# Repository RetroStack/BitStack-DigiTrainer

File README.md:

# DigiTrainer

As part of an introduction in digital electronics workshop at VCF SW 2024, I prepared this board. The intent was to reduce lookup time for datasheets and being able to just connect the inputs and outputs of various gates and logic ICs without caring too much about power supplies. In addition, this board features DIP-switches, a toggle and slide switch, hexadecimal switches, LED arrays which do have a built in resistor for current limiting, pull-up and -down resistors, and much more.

In addition to all of that, it includes a section for a Z80 CPU, static memory, and a ROM to be able to learn to program and work with 8-bit CPUs.

## Latest Files

In the "Latest" folder, you'll find the most up-to-date design files, including:

- Gerber files suitable for popular online PCB manufacturers like [PCBWay](/Latest/DigiTrainer_Gerber_PCBWay.zip) and [JLCPCB](/Latest/DigiTrainer_Gerber_JLCPCB.zip). Most manufacturers should be fine with either.
- A Bill of Materials (BOM) in both [CSV](/Latest/DigiTrainer_BOM.csv) and [PDF](/Latest/DigiTrainer_BOM.pdf) formats.
- The [full schematics](/Latest/DigiTrainer_Schematics.pdf) of the board.

## Implementation

The board has been implemented using KiCAD 8. The KiCAD project files are included in this repository.

## How to Use

All inputs of various ICs and gates are on the left side of the indicated gate or IC, while outputs are on the right side of the silkscreen indications. Bi-directional pins are horizontal or on the output side (such as at the Z80 CPU for the data bus).

Many components are already connected to +5V or GND and are indicated by an "arrow up" and "triangle down" respectively. Keep in mind that an LED connected to an IC output with +5V acts as an inverted output due to current sinking.

The top right area also provides a legend of common rules/laws and symbols used in digital electronics (and logic as an extension of it).

## Bill of Materials (BOM)

Below is a list of materials needed to assemble the PCB.

| Reference                                                                                                                                                                                                                                                                                                  | Qty | Description         | Footprint                                                  | Datasheet                                                    |
| ---------------------------------------------------------------------------------------------------------------------------------------------------------------------------------------------------------------------------------------------------------------------------------------------------------- | --- | ------------------- | ---------------------------------------------------------- | ------------------------------------------------------------ |
| C1,C2,C3,C4,C5,C6,C7,C8,C9,C10,C11,C12,C13,C14,C15,C16,C17,C18,C19,C20,C25,C26,C27,C28,C29,C30                                                                                                                                                                                                             | 26  | 0.1uF               | Capacitor_SMD:C_0805_2012Metric_Pad1.18x1.45mm_HandSolder  | ~                                                            |
| C21,C24                                                                                                                                                                                                                                                                                                    | 2   | 1uF                 | Capacitor_SMD:C_0805_2012Metric_Pad1.18x1.45mm_HandSolder  | ~                                                            |
| C22,C23                                                                                                                                                                                                                                                                                                    | 2   | 0.01uF              | Capacitor_SMD:C_0805_2012Metric_Pad1.18x1.45mm_HandSolder  | ~                                                            |
| D1,D2                                                                                                                                                                                                                                                                                                      | 2   | D_Schottky          | Diode_THT:D_DO-41_SOD81_P7.62mm_Horizontal                 | ~                                                            |
| DN1,DN2,DN3                                                                                                                                                                                                                                                                                                | 3   | LED Array           | Package_DIP:DIP-20_W7.62mm_Socket                          | ~                                                            |
| J1,J2,J86,J158,J159,J160                                                                                                                                                                                                                                                                                   | 6   | Conn_01x10          | Connector_PinSocket_2.54mm:PinSocket_1x10_P2.54mm_Vertical | ~                                                            |
| J3,J16,J17,J18,J19,J20,J21,J22,J23,J24,J25,J26,J27,J28,J29,J30,J31,J54,J55,J56,J57,J58,J59,J60,J61,J62,J63,J64,J65,J66,J67,J68,J69,J89,J99,J100,J102,J109,J110,J111,J112,J113,J114,J122,J123,J125,J126,J133,J137,J138,J142,J144,J145,J146,J147,J148,J149,J150,J151,J152,J153,J154,J155,J156,J157,J163,J168 | 67  | Conn_01x02          | Connector_PinSocket_2.54mm:PinSocket_1x02_P2.54mm_Vertical | ~                                                            |
| J4,J5,J6,J7,J8,J9,J10,J11,J12,J13,J14,J15,J32,J33,J34,J35,J36,J37,J38,J39,J40,J41,J42,J43,J44,J45,J46,J47,J48,J49,J50,J51,J52,J53,J70,J71,J72,J73,J74,J75,J76,J77,J78,J79,J80,J81,J87,J106,J107,J108,J135,J136,J141,J143,J167,J169                                                                         | 56  | Conn_01x03          | Connector_PinSocket_2.54mm:PinSocket_1x03_P2.54mm_Vertical | ~                                                            |
| J82,J83,J84,J85,J98,J103,J121,J124,J161,J162                                                                                                                                                                                                                                                               | 10  | Conn_01x06          | Connector_PinSocket_2.54mm:PinSocket_1x06_P2.54mm_Vertical | ~                                                            |
| J88,J90,J91,J101,J104,J105,J164,J165,J166,J173,J174                                                                                                                                                                                                                                                        | 11  | Conn_01x08          | Connector_PinSocket_2.54mm:PinSocket_1x08_P2.54mm_Vertical | ~                                                            |
| J92,J93,J94,J172                                                                                                                                                                                                                                                                                           | 4   | Conn_02x02_Odd_Even | Connector_PinHeader_2.54mm:PinHeader_2x02_P2.54mm_Vertical | ~                                                            |
| J95                                                                                                                                                                                                                                                                                                        | 1   | Barrel_Jack_Switch  | Connector_BarrelJack:BarrelJack_Horizontal                 | ~                                                            |
| J96                                                                                                                                                                                                                                                                                                        | 1   | USB_B_Mini          | Connector_USB:USB_Mini-B_Tensility_54-00023_Vertical       | ~                                                            |
| J97,J115,J117,J127,J128,J129,J130,J131,J132,J139,J140,J170,J171                                                                                                                                                                                                                                            | 13  | Conn_01x04          | Connector_PinSocket_2.54mm:PinSocket_1x04_P2.54mm_Vertical | ~                                                            |
| J116,J118,J119,J120,J134                                                                                                                                                                                                                                                                                   | 5   | Conn_01x05          | Connector_PinSocket_2.54mm:PinSocket_1x05_P2.54mm_Vertical | ~                                                            |
| R1,R2,R3                                                                                                                                                                                                                                                                                                   | 3   | 10k                 | Resistor_SMD:R_0805_2012Metric_Pad1.20x1.40mm_HandSolder   | ~                                                            |
| R4,R5,R6,R7                                                                                                                                                                                                                                                                                                | 4   | 1k                  | Resistor_SMD:R_0805_2012Metric_Pad1.20x1.40mm_HandSolder   | ~                                                            |
| RN1,RN2,RN3,RN4,RN5                                                                                                                                                                                                                                                                                        | 5   | R_Network10         | Resistor_THT:R_Array_SIP11                                 | http://www.vishay.com/docs/31509/csc.pdf                     |
| RV1                                                                                                                                                                                                                                                                                                        | 1   | R_Potentiometer     | Potentiometer_THT:Potentiometer_Bourns_3386P_Vertical      | ~                                                            |
| RV2                                                                                                                                                                                                                                                                                                        | 1   | 1M                  | Potentiometer_THT:Potentiometer_Bourns_3386P_Vertical      | ~                                                            |
| SW1,SW5,SW6,SW7,SW8                                                                                                                                                                                                                                                                                        | 5   | SW_Push             | RetroStackLibrary:SW_SPST_Push                             | ~                                                            |
| SW2                                                                                                                                                                                                                                                                                                        | 1   | SW_DPDT_x2          | RetroStackLibrary:SW_DPDT_Push                             | ~                                                            |
| SW3,SW4                                                                                                                                                                                                                                                                                                    | 2   | SW_DIP_x04          | Package_DIP:DIP-8_W7.62mm                                  | ~                                                            |
| SW9                                                                                                                                                                                                                                                                                                        | 1   | SW_SPDT             | RetroStackLibrary:SW_SPDT_Toggle                           | ~                                                            |
| SW10                                                                                                                                                                                                                                                                                                       | 1   | SW_Push_DPDT        | RetroStackLibrary:SW_DPDT_Slide_RightAngle                 | ~                                                            |
| SW11,SW12                                                                                                                                                                                                                                                                                                  | 2   | Hex Switch          | RetroStackLibrary:SW_Hexadecimal_Horizontal                | https://www.ckswitches.com/media/1333/cd.pdf                 |
| U1                                                                                                                                                                                                                                                                                                         | 1   | 74LS07              | Package_SO:SOIC-14_3.9x8.7mm_P1.27mm                       | www.ti.com/lit/ds/symlink/sn74ls07.pdf                       |
| U2                                                                                                                                                                                                                                                                                                         | 1   | 74LS04              | Package_SO:SOIC-14_3.9x8.7mm_P1.27mm                       | http://www.ti.com/lit/gpn/sn74LS04                           |
| U3                                                                                                                                                                                                                                                                                                         | 1   | 74LS266             | Package_SO:SOIC-14_3.9x8.7mm_P1.27mm                       | ~                                                            |
| U4,U5                                                                                                                                                                                                                                                                                                      | 2   | 74LS00              | Package_SO:SOIC-14_3.9x8.7mm_P1.27mm                       | http://www.ti.com/lit/gpn/sn74ls00                           |
| U6                                                                                                                                                                                                                                                                                                         | 1   | 74LS08              | Package_SO:SOIC-14_3.9x8.7mm_P1.27mm                       | http://www.ti.com/lit/gpn/sn74LS08                           |
| U7                                                                                                                                                                                                                                                                                                         | 1   | 74LS86              | Package_SO:SOIC-14_3.9x8.7mm_P1.27mm                       | 74xx/74ls86.pdf                                              |
| U8                                                                                                                                                                                                                                                                                                         | 1   | 74LS32              | Package_SO:SOIC-14_3.9x8.7mm_P1.27mm                       | http://www.ti.com/lit/gpn/sn74LS32                           |
| U9                                                                                                                                                                                                                                                                                                         | 1   | 74LS02              | Package_SO:SOIC-14_3.9x8.7mm_P1.27mm                       | http://www.ti.com/lit/gpn/sn74ls02                           |
| U10                                                                                                                                                                                                                                                                                                        | 1   | 74LS244             | Package_SO:SOIC-20W_7.5x12.8mm_P1.27mm                     | http://www.ti.com/lit/ds/symlink/sn74ls244.pdf               |
| U11                                                                                                                                                                                                                                                                                                        | 1   | 74LS245             | Package_SO:SO-20_5.3x12.6mm_P1.27mm                        | http://www.ti.com/lit/gpn/sn74LS245                          |
| U12                                                                                                                                                                                                                                                                                                        | 1   | 74LS51              | Package_SO:SOIC-14_3.9x8.7mm_P1.27mm                       | http://www.ti.com/lit/ds/symlink/sn74ls51.pdf                |
| U13                                                                                                                                                                                                                                                                                                        | 1   | 74LS174             | Package_SO:SOIC-16_3.9x9.9mm_P1.27mm                       | http://www.ti.com/lit/gpn/sn74LS174                          |
| U14                                                                                                                                                                                                                                                                                                        | 1   | 74LS175             | Package_SO:SOIC-16_3.9x9.9mm_P1.27mm                       | http://www.ti.com/lit/gpn/sn74LS175                          |
| U15                                                                                                                                                                                                                                                                                                        | 1   | 74LS373             | Package_SO:SO-20_5.3x12.6mm_P1.27mm                        | http://www.ti.com/lit/gpn/sn74LS373                          |
| U16                                                                                                                                                                                                                                                                                                        | 1   | 74LS112             | Package_SO:SOIC-16_3.9x9.9mm_P1.27mm                       | http://www.ti.com/lit/gpn/sn74LS112                          |
| U17                                                                                                                                                                                                                                                                                                        | 1   | 74LS107             | Package_SO:SOIC-14_3.9x8.7mm_P1.27mm                       | http://www.ti.com/lit/gpn/sn74LS107                          |
| U18                                                                                                                                                                                                                                                                                                        | 1   | 74LS161             | Package_SO:SOIC-16_3.9x9.9mm_P1.27mm                       | http://www.ti.com/lit/gpn/sn74LS161                          |
| U19                                                                                                                                                                                                                                                                                                        | 1   | 74LS163             | Package_SO:SOIC-16_3.9x9.9mm_P1.27mm                       | http://www.ti.com/lit/gpn/sn74LS163                          |
| U20,U21                                                                                                                                                                                                                                                                                                    | 2   | 74LS194             | Package_SO:SOIC-16_3.9x9.9mm_P1.27mm                       | http://www.ti.com/lit/gpn/sn74LS194                          |
| U22                                                                                                                                                                                                                                                                                                        | 1   | 74LS283             | Package_SO:SOIC-16_3.9x9.9mm_P1.27mm                       | http://www.ti.com/lit/gpn/sn74LS283                          |
| U23                                                                                                                                                                                                                                                                                                        | 1   | 74LS85              | Package_SO:SOIC-16_3.9x9.9mm_P1.27mm                       | http://www.ti.com/lit/gpn/sn74LS85                           |
| U24                                                                                                                                                                                                                                                                                                        | 1   | NE556               | Package_SO:SOIC-14_3.9x8.7mm_P1.27mm                       | http://www.ti.com/lit/ds/symlink/ne556.pdf                   |
| U25                                                                                                                                                                                                                                                                                                        | 1   | Z80CPU              | Package_DIP:DIP-40_W15.24mm_Socket                         | www.zilog.com/manage_directlink.php?filepath=docs/z80/um0080 |
| U26                                                                                                                                                                                                                                                                                                        | 1   | ROM_27256           | Package_DIP:DIP-28_W15.24mm                                | ~                                                            |
| U27                                                                                                                                                                                                                                                                                                        | 1   | CY7C199             | Package_DIP:DIP-28_W7.62mm                                 | ~                                                            |

## RetroStack Libraries

To work with this KiCAD project, you'll need the RetroStack libraries for KiCAD. Please [follow this link](https://www.github.com/RetroStack/KiCAD-Libraries) to access and install these libraries.

## Support this Project

RetroStack is passionate about exploring and preserving the legacy of older computer systems. BitStack is a sub-project of RetroStack, focusing on education in digital electronics. My work involves creating detailed documentation and videos to share the knowledge. I am also dedicated to reviving these classic systems by reimplementing them and offering replacement parts at no cost. If you're keen on supporting this unique project, I invite you to visit my [Patreon page](https://www.patreon.com/RetroStack). Your support would be immensely valuable and greatly appreciated!

## License

This project is licensed under the MIT License - see the [LICENSE](LICENSE) file for details.

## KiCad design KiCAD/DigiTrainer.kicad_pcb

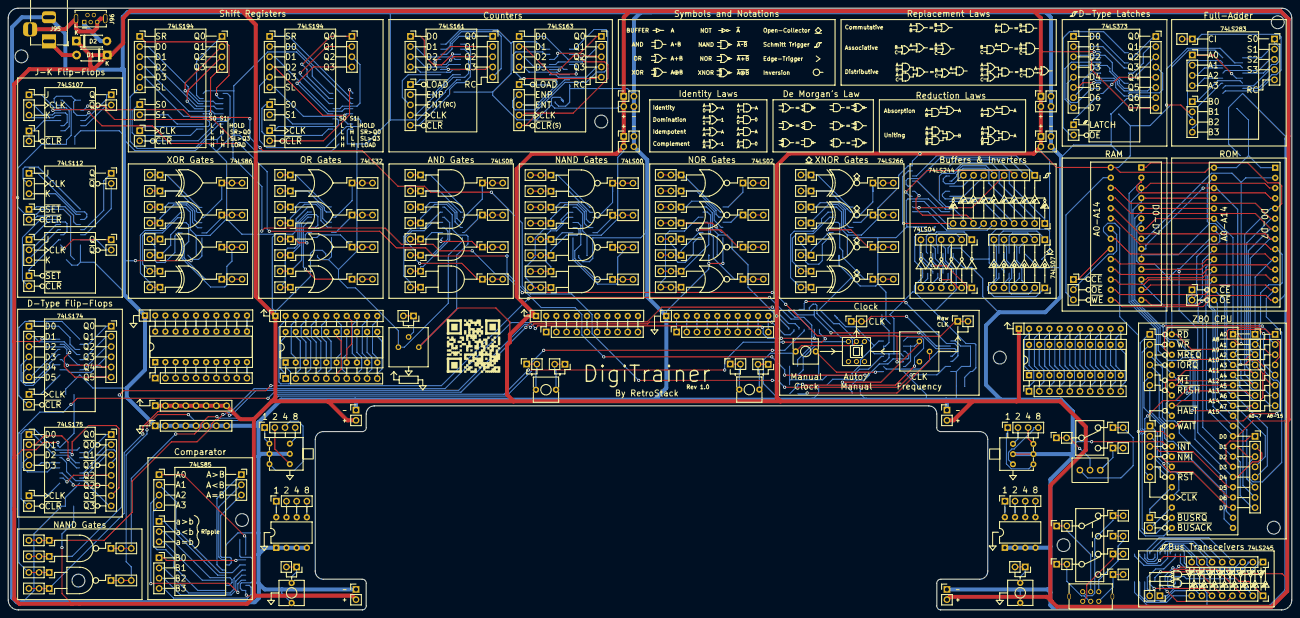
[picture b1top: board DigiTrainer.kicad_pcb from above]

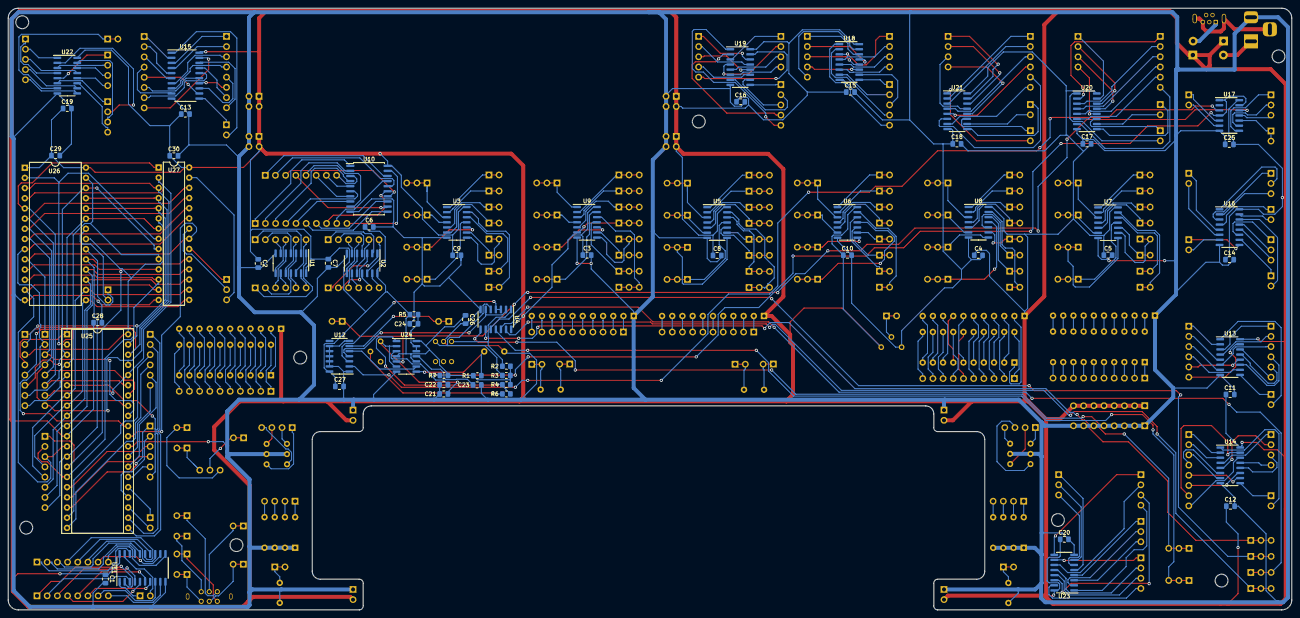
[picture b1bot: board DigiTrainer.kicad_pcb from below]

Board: 2 copper layers, 320.0 x 150.0 mm, 262 parts (64 on the bottom side), 464 nets.

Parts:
C1, C2, C3, C4, C5, C6, C7, C8, C9, C10, C11, C12, C13, C14, C15, C16, C17, C18, C19, C20, C25, C26, C27, C28, C29, C30: 0.1uF; C_0805_2012Metric_Pad1.18x1.45mm_HandSolder
C21, C24: 1uF; C_0805_2012Metric_Pad1.18x1.45mm_HandSolder
C22, C23: 0.01uF; C_0805_2012Metric_Pad1.18x1.45mm_HandSolder
D1, D2: D_Schottky; D_DO-41_SOD81_P7.62mm_Horizontal
DN1, DN2, DN3: DIP-20_W7.62mm_Socket
J1, J2, J86, J158, J159, J160: Conn_01x10; PinSocket_1x10_P2.54mm_Vertical
J3, J16, J17, J18, J19, J20, J21, J22, J23, J24, J25, J26, J27, J28, J29, J30, J31, J54, J55, J56, J57, J58, J59, J60, J61, J62, J63, J64, J65, J66, J67, J68, J69, J133, J137, J138, J142, J144, J145, J146, J147, J148, J149, J150, J151, J152, J153, J154, J155, J156, J157: PinSocket_1x02_P2.54mm_Vertical
J4, J5, J6, J7, J8, J9, J10, J11, J12, J13, J14, J15, J32, J33, J34, J35, J36, J37, J38, J39, J40, J41, J42, J43, J44, J45, J46, J47, J48, J49, J50, J51, J52, J53, J70, J71, J72, J73, J74, J75, J76, J77, J78, J79, J80, J81: PinSocket_1x03_P2.54mm_Vertical
J82, J83, J84, J85, J98, J103, J121, J124, J161, J162: Conn_01x06; PinSocket_1x06_P2.54mm_Vertical
J87, J141, J143, J169: Conn_02x01; PinHeader_1x02_P2.54mm_Vertical
J88, J90, J91, J101, J104, J105, J164, J165, J166, J173, J174: Conn_01x08; PinSocket_1x08_P2.54mm_Vertical
J89, J99, J100, J102, J109, J110, J111, J112, J113, J114, J122, J123, J125, J126, J163, J168: Conn_01x02; PinSocket_1x02_P2.54mm_Vertical
J92, J93, J94, J172: Conn_02x02_Odd_Even; PinHeader_2x02_P2.54mm_Vertical
J95: Barrel_Jack_Switch; BarrelJack_Horizontal
J96: USB_B_Mini; USB_Mini-B_Tensility_54-00023_Vertical
J97, J115, J117, J127, J128, J129, J130, J131, J132, J139, J140, J170, J171: Conn_01x04; PinSocket_1x04_P2.54mm_Vertical
J106, J107, J108, J135, J136, J167: Conn_01x03; PinSocket_1x03_P2.54mm_Vertical
J116, J118, J119, J120, J134: Conn_01x05; PinSocket_1x05_P2.54mm_Vertical
R1, R2, R3: 10k; R_0805_2012Metric_Pad1.20x1.40mm_HandSolder
R4, R5, R6, R7: 1k; R_0805_2012Metric_Pad1.20x1.40mm_HandSolder
RN1, RN2, RN3, RN4, RN5: R_Network10; R_Array_SIP11
RV1: R_Potentiometer; Potentiometer_Bourns_3386P_Vertical
RV2: 1M; Potentiometer_Bourns_3386P_Vertical
SW1, SW5, SW6, SW7, SW8: SW_Push; SW_SPST_Push
SW2: SW_DPDT_x2; SW_DPDT_Push
SW3, SW4: SW_DIP_x04; DIP-8_W7.62mm
SW9: SW_SPDT; SW_SPDT_Toggle
SW10: SW_Push_DPDT; SW_DPDT_Slide_RightAngle
SW11, SW12: SW_Hexadecimal_Horizontal
U1: 74LS07; SOIC-14_3.9x8.7mm_P1.27mm
U2: 74LS04; SOIC-14_3.9x8.7mm_P1.27mm
U3: 74LS266; SOIC-14_3.9x8.7mm_P1.27mm
U4, U5: 74LS00; SOIC-14_3.9x8.7mm_P1.27mm
U6: 74LS08; SOIC-14_3.9x8.7mm_P1.27mm
U7: 74LS86; SOIC-14_3.9x8.7mm_P1.27mm
U8: 74LS32; SOIC-14_3.9x8.7mm_P1.27mm
U9: 74LS02; SOIC-14_3.9x8.7mm_P1.27mm
U10: 74LS244; SOIC-20W_7.5x12.8mm_P1.27mm
U11: 74LS245; SO-20_5.3x12.6mm_P1.27mm
U12: 74LS51; SOIC-14_3.9x8.7mm_P1.27mm
U13: 74LS174; SOIC-16_3.9x9.9mm_P1.27mm
U14: 74LS175; SOIC-16_3.9x9.9mm_P1.27mm
U15: 74LS373; SO-20_5.3x12.6mm_P1.27mm
U16: 74LS112; SOIC-16_3.9x9.9mm_P1.27mm
U17: 74LS107; SOIC-14_3.9x8.7mm_P1.27mm
U18: 74LS161; SOIC-16_3.9x9.9mm_P1.27mm
U19: 74LS163; SOIC-16_3.9x9.9mm_P1.27mm
U20, U21: 74LS194; SOIC-16_3.9x9.9mm_P1.27mm
U22: 74LS283; SOIC-16_3.9x9.9mm_P1.27mm
U23: 74LS85; SOIC-16_3.9x9.9mm_P1.27mm
U24: NE556; SOIC-14_3.9x8.7mm_P1.27mm
U25: Z80CPU; DIP-40_W15.24mm_Socket
U26: ROM_27256; DIP-28_W15.24mm
U27: CY7C199; DIP-28_W7.62mm

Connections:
+5V: C1.1, C2.1, C3.1, C4.1, C5.1, C6.1, C7.1, C8.1, C9.1, C10.1, C11.1, C12.1, C13.1, C14.1, C15.1, C16.1, C17.1, C18.1, C19.1, C20.1, C25.1, C26.1, C27.1, C28.1, C29.1, C30.1, D1.1 (K), D2.1 (K), J87.2, J92.1, J92.3, J93.1, J93.3, J94.1, J94.3, J141.2, J143.2, J169.2, J172.1, J172.3, J173.1, J173.2, J173.3, J173.4, J173.5, J173.6, J173.7, J173.8, R1.2, R2.1, R3.2, R4.1, R5.1, R7.1, RN2.1 (common), RN3.1 (common), RN5.1 (common), RV1.1, U1.14 (VCC), U2.14 (VCC), U3.14 (VCC), U4.14 (VCC), U5.14 (VCC), U6.14 (VCC), U7.14 (VCC), U8.14 (VCC), U9.14 (VCC), U10.20 (VCC), U11.20 (VCC), U12.14 (VCC), U13.16 (VCC), U14.16 (VCC), U15.20 (VCC), U16.16 (VCC), U17.14 (VCC), U18.16 (VCC), U19.16 (VCC), U20.16 (VCC), U21.16 (VCC), U22.16 (VCC), U23.16 (VCC), U24.4 (R), U24.10 (R), U24.14 (VCC), U25.11 (VCC), U26.1 (VPP), U26.28 (VCC), U27.28 (VCC)
/CPU/A0: J164.1, U25.30 (A0), U26.10 (A0), U27.21 (A0)
/CPU/A1: J164.2, U25.31 (A1), U26.9 (A1), U27.23 (A1)
/CPU/A2: J164.3, U25.32 (A2), U26.8 (A2), U27.24 (A2)
/CPU/A3: J164.4, U25.33 (A3), U26.7 (A3), U27.25 (A3)
/CPU/A4: J164.5, U25.34 (A4), U26.6 (A4), U27.26 (A4)
/CPU/A5: J164.6, U25.35 (A5), U26.5 (A5), U27.1 (A5)
/CPU/A6: J164.7, U25.36 (A6), U26.4 (A6), U27.2 (A6)
/CPU/A7: J164.8, U25.37 (A7), U26.3 (A7), U27.3 (A7)
/CPU/A8: J165.1, U25.38 (A8), U26.25 (A8), U27.4 (A8)
/CPU/A9: J165.2, U25.39 (A9), U26.24 (A9), U27.5 (A9)
/CPU/A10: J165.3, U25.40 (A10), U26.21 (A10), U27.6 (A10)
/CPU/A11: J165.4, U25.1 (A11), U26.23 (A11), U27.7 (A11)
/CPU/A12: J165.5, U25.2 (A12), U26.2 (A12), U27.8 (A12)
/CPU/A13: J165.6, U25.3 (A13), U26.26 (A13), U27.9 (A13)
/CPU/A14: J165.7, U25.4 (A14), U26.27 (A14), U27.10 (A14)
/CPU/A15: J165.8, U25.5 (A15)
/CPU/D0: J166.1, U25.14 (D0), U26.11 (D0), U27.11 (D0)
/CPU/D1: J166.2, U25.15 (D1), U26.12 (D1), U27.12 (D1)
/CPU/D2: J166.3, U25.12 (D2), U26.13 (D2), U27.13 (D2)
/CPU/D3: J166.4, U25.8 (D3), U26.15 (D3), U27.15 (D3)
/CPU/D4: J166.5, U25.7 (D4), U26.16 (D4), U27.16 (D4)
/CPU/D5: J166.6, U25.9 (D5), U26.17 (D5), U27.17 (D5)
/CPU/D6: J166.7, U25.10 (D6), U26.18 (D6), U27.18 (D6)
/CPU/D7: J166.8, U25.13 (D7), U26.19 (D7), U27.19 (D7)
GND: C1.2, C2.2, C3.2, C4.2, C5.2, C6.2, C7.2, C8.2, C9.2, C10.2, C11.2, C12.2, C13.2, C14.2, C15.2, C16.2, C17.2, C18.2, C19.2, C20.2, C21.1, C22.1, C23.1, C24.2, C25.2, C26.2, C27.2, C28.2, C29.2, C30.2, J87.1, J92.2, J92.4, J93.2, J93.4, J94.2, J94.4, J95.2, J141.1, J143.1, J169.1, J172.2, J172.4, J174.1, J174.2, J174.3, J174.4, J174.5, J174.6, J174.7, J174.8, RN1.1 (common), RN4.1 (common), RV1.3, SW1.1, SW2.2 (B), SW3.1, SW3.2, SW3.3, SW3.4, SW4.1, SW4.2, SW4.3, SW4.4, SW5.1, SW7.1, SW11.1 (C), SW12.1 (C), U1.7 (GND), U2.7 (GND), U3.7 (GND), U4.7 (GND), U5.7 (GND), U6.7 (GND), U7.7 (GND), U8.7 (GND), U9.7 (GND), U10.10 (GND), U11.10 (GND), U12.1, U12.7 (GND), U12.9, U12.10, U12.11, U12.12, U12.13, U13.8 (GND), U14.8 (GND), U15.10 (GND), U16.8 (GND), U17.7 (GND), U18.8 (GND), U19.8 (GND), U20.8 (GND), U21.8 (GND), U22.8 (GND), U23.8 (GND), U24.7 (GND), U25.29 (GND), U26.14 (GND), U27.14 (GND)
unnamed: D1.2 (A), J95.1
unnamed: D2.2 (A), J96.1 (VBUS)
unnamed: J1.1, RN1.2 (R1)
unnamed: J1.2, RN1.3 (R2)
unnamed: J1.3, RN1.4 (R3)
unnamed: J1.4, RN1.5 (R4)
unnamed: J1.5, RN1.6 (R5)
unnamed: J1.6, RN1.7 (R6)
unnamed: J1.7, RN1.8 (R7)
unnamed: J1.8, RN1.9 (R8)
unnamed: J1.9, RN1.10 (R9)
unnamed: J1.10, RN1.11 (R10)
unnamed: J2.1, RN2.2 (R1)
unnamed: J2.2, RN2.3 (R2)
unnamed: J2.3, RN2.4 (R3)
unnamed: J2.4, RN2.5 (R4)
unnamed: J2.5, RN2.6 (R5)
unnamed: J2.6, RN2.7 (R6)
unnamed: J2.7, RN2.8 (R7)
unnamed: J2.8, RN2.9 (R8)
unnamed: J2.9, RN2.10 (R9)
unnamed: J2.10, RN2.11 (R10)
unnamed: J3.1, J3.2, RV1.2
unnamed: J4.1, J4.2, J4.3, U4.9
unnamed: J5.1, J5.2, J5.3, U4.10
unnamed: J6.1, J6.2, J6.3, U4.12
unnamed: J7.1, J7.2, J7.3, U4.13
unnamed: J8.1, J8.2, J8.3, U5.1
unnamed: J9.1, J9.2, J9.3, U5.2
unnamed: J10.1, J10.2, J10.3, U5.4
unnamed: J11.1, J11.2, J11.3, U5.5
unnamed: J12.1, J12.2, J12.3, U5.9
unnamed: J13.1, J13.2, J13.3, U5.10
unnamed: J14.1, J14.2, J14.3, U5.12
unnamed: J15.1, J15.2, J15.3, U5.13
unnamed: J16.1, J16.2, U6.1
unnamed: J17.1, J17.2, U6.2
unnamed: J18.1, J18.2, U6.4
unnamed: J19.1, J19.2, U6.5
unnamed: J20.1, J20.2, U6.9
unnamed: J21.1, J21.2, U6.10
unnamed: J22.1, J22.2, U6.12
unnamed: J23.1, J23.2, U6.13
unnamed: J24.1, J24.2, U7.1
unnamed: J25.1, J25.2, U7.2
unnamed: J26.1, J26.2, U7.4
unnamed: J27.1, J27.2, U7.5
unnamed: J28.1, J28.2, U7.9
unnamed: J29.1, J29.2, U7.10
unnamed: J30.1, J30.2, U7.12
unnamed: J31.1, J31.2, U7.13
unnamed: J32.1, J32.2, J32.3, U4.8
unnamed: J33.1, J33.2, J33.3, U4.11
unnamed: J34.1, J34.2, J34.3, U5.3
unnamed: J35.1, J35.2, J35.3, U5.6
unnamed: J36.1, J36.2, J36.3, U5.8
unnamed: J37.1, J37.2, J37.3, U5.11
unnamed: J38.1, J38.2, J38.3, U6.3
unnamed: J39.1, J39.2, J39.3, U6.6
unnamed: J40.1, J40.2, J40.3, U6.8
unnamed: J41.1, J41.2, J41.3, U6.11
unnamed: J42.1, J42.2, J42.3, U7.3
unnamed: J43.1, J43.2, J43.3, U7.6
unnamed: J44.1, J44.2, J44.3, U7.8
unnamed: J45.1, J45.2, J45.3, U7.11
unnamed: J46.1, J46.2, J46.3, U9.2
unnamed: J47.1, J47.2, J47.3, U9.3
unnamed: J48.1, J48.2, J48.3, U9.5
unnamed: J49.1, J49.2, J49.3, U9.6
unnamed: J50.1, J50.2, J50.3, U9.8
unnamed: J51.1, J51.2, J51.3, U9.9
unnamed: J52.1, J52.2, J52.3, U9.11
unnamed: J53.1, J53.2, J53.3, U9.12
unnamed: J54.1, J54.2, U8.1
unnamed: J55.1, J55.2, U8.2
unnamed: J56.1, J56.2, U8.4
unnamed: J57.1, J57.2, U8.5
unnamed: J58.1, J58.2, U8.9
unnamed: J59.1, J59.2, U8.10
unnamed: J60.1, J60.2, U8.12
unnamed: J61.1, J61.2, U8.13
unnamed: J62.1, J62.2, U3.1
unnamed: J63.1, J63.2, U3.2
unnamed: J64.1, J64.2, U3.5
unnamed: J65.1, J65.2, U3.6
unnamed: J66.1, J66.2, U3.8
unnamed: J67.1, J67.2, U3.9
unnamed: J68.1, J68.2, U3.12
unnamed: J69.1, J69.2, U3.13
unnamed: J70.1, J70.2, J70.3, U9.1
unnamed: J71.1, J71.2, J71.3, U9.4
unnamed: J72.1, J72.2, J72.3, U9.10
unnamed: J73.1, J73.2, J73.3, U9.13
unnamed: J74.1, J74.2, J74.3, U8.3
unnamed: J75.1, J75.2, J75.3, U8.6
unnamed: J76.1, J76.2, J76.3, U8.8
unnamed: J77.1, J77.2, J77.3, U8.11
unnamed: J78.1, J78.2, J78.3, U3.3
unnamed: J79.1, J79.2, J79.3, U3.4
unnamed: J80.1, J80.2, J80.3, U3.10
unnamed: J81.1, J81.2, J81.3, U3.11
unnamed: J82.1, U1.1
unnamed: J82.2, U1.3
unnamed: J82.3, U1.5
unnamed: J82.4, U1.9
unnamed: J82.5, U1.11
unnamed: J82.6, U1.13
unnamed: J83.1, U2.1
unnamed: J83.2, U2.3
unnamed: J83.3, U2.5
unnamed: J83.4, U2.9
unnamed: J83.5, U2.11
unnamed: J83.6, U2.13
unnamed: J84.1, U1.2
unnamed: J84.2, U1.4
unnamed: J84.3, U1.6
unnamed: J84.4, U1.8
unnamed: J84.5, U1.10
unnamed: J84.6, U1.12
unnamed: J85.1, U2.2
unnamed: J85.2, U2.4
unnamed: J85.3, U2.6
unnamed: J85.4, U2.8
unnamed: J85.5, U2.10
unnamed: J85.6, U2.12
unnamed: J86.1, U10.1 (OEa)
unnamed: J86.2, U10.2 (I0a)
unnamed: J86.3, U10.4 (I1a)
unnamed: J86.4, U10.6 (I2a)
unnamed: J86.5, U10.8 (I3a)
unnamed: J86.6, U10.11 (I0b)
unnamed: J86.7, U10.13 (I1b)
unnamed: J86.8, U10.15 (I2b)
unnamed: J86.9, U10.17 (I3b)
unnamed: J86.10, U10.19 (OEb)
unnamed: J88.1, U11.2 (A0)
unnamed: J88.2, U11.3 (A1)
unnamed: J88.3, U11.4 (A2)
unnamed: J88.4, U11.5 (A3)
unnamed: J88.5, U11.6 (A4)
unnamed: J88.6, U11.7 (A5)
unnamed: J88.7, U11.8 (A6)
unnamed: J88.8, U11.9 (A7)
unnamed: J89.1, U11.1 (A->B)
unnamed: J89.2, U11.19 (CE)
unnamed: J90.1, U10.18 (O0a)
unnamed: J90.2, U10.16 (O1a)
unnamed: J90.3, U10.14 (O2a)
unnamed: J90.4, U10.12 (O3a)
unnamed: J90.5, U10.9 (O0b)
unnamed: J90.6, U10.7 (O1b)
unnamed: J90.7, U10.5 (O2b)
unnamed: J90.8, U10.3 (O3b)
unnamed: J91.1, U11.18 (B0)
unnamed: J91.2, U11.17 (B1)
unnamed: J91.3, U11.16 (B2)
unnamed: J91.4, U11.15 (B3)
unnamed: J91.5, U11.14 (B4)
unnamed: J91.6, U11.13 (B5)
unnamed: J91.7, U11.12 (B6)
unnamed: J91.8, U11.11 (B7)
unnamed: J95.3, J96.5 (GND), J96.6 (Shield)
unnamed: J97.1, U14.4 (D0)
unnamed: J97.2, U14.5 (D1)
unnamed: J97.3, U14.12 (D2)
unnamed: J97.4, U14.13 (D3)
unnamed: J98.1, U13.3 (D0)
unnamed: J98.2, U13.4 (D1)
unnamed: J98.3, U13.6 (D2)
unnamed: J98.4, U13.11 (D3)
unnamed: J98.5, U13.13 (D4)
unnamed: J98.6, U13.14 (D5)
unnamed: J99.1, U13.9 (Cp)
unnamed: J99.2, U13.1 (~Mr)
unnamed: J100.1, U14.9 (Cp)
unnamed: J100.2, U14.1 (~Mr)
unnamed: J101.1, U15.3 (D0)
unnamed: J101.2, U15.4 (D1)
unnamed: J101.3, U15.7 (D2)
unnamed: J101.4, U15.8 (D3)
unnamed: J101.5, U15.13 (D4)
unnamed: J101.6, U15.14 (D5)
unnamed: J101.7, U15.17 (D6)
unnamed: J101.8, U15.18 (D7)
unnamed: J102.1, U15.11 (LE)
unnamed: J102.2, U15.1 (OE)
unnamed: J103.1, U13.2 (Q0)
unnamed: J103.2, U13.5 (Q1)
unnamed: J103.3, U13.7 (Q2)
unnamed: J103.4, U13.10 (Q3)
unnamed: J103.5, U13.12 (Q4)
unnamed: J103.6, U13.15 (Q5)
unnamed: J104.1, U14.2 (Q0)
unnamed: J104.2, U14.3 (~Q0)
unnamed: J104.3, U14.7 (Q1)
unnamed: J104.4, U14.6 (~Q1)
unnamed: J104.5, U14.10 (Q2)
unnamed: J104.6, U14.11 (~Q2)
unnamed: J104.7, U14.15 (Q3)
unnamed: J104.8, U14.14 (~Q3)
unnamed: J105.1, U15.2 (O0)
unnamed: J105.2, U15.5 (O1)
unnamed: J105.3, U15.6 (O2)
unnamed: J105.4, U15.9 (O3)
unnamed: J105.5, U15.12 (O4)
unnamed: J105.6, U15.15 (O5)
unnamed: J105.7, U15.16 (O6)
unnamed: J105.8, U15.19 (O7)
unnamed: J106.1, U17.8 (J)
unnamed: J106.2, U17.9 (C)
unnamed: J106.3, U17.11 (K)
unnamed: J107.1, U16.3 (J)
unnamed: J107.2, U16.1 (C)
unnamed: J107.3, U16.2 (K)
unnamed: J108.1, U16.11 (J)
unnamed: J108.2, U16.13 (C)
unnamed: J108.3, U16.12 (K)
unnamed: J109.1, U17.5 (Q)
unnamed: J109.2, U17.6 (~Q)
unnamed: J110.1, J110.2, U17.10 (~R)
unnamed: J111.1, U16.5 (Q)
unnamed: J111.2, U16.6 (~Q)
unnamed: J112.1, U16.9 (Q)
unnamed: J112.2, U16.7 (~Q)
unnamed: J113.1, U16.4 (~S)
unnamed: J113.2, U16.15 (~R)
unnamed: J114.1, U16.10 (~S)
unnamed: J114.2, U16.14 (~R)
unnamed: J115.1, U18.3 (D0)
unnamed: J115.2, U18.4 (D1)
unnamed: J115.3, U18.5 (D2)
unnamed: J115.4, U18.6 (D3)
unnamed: J116.1, U18.9 (~PE)
unnamed: J116.2, U18.7 (CEP)
unnamed: J116.3, U18.10 (CET)
unnamed: J116.4, U18.2 (CP)
unnamed: J116.5, U18.1 (~MR)
unnamed: J117.1, U19.3 (D0)
unnamed: J117.2, U19.4 (D1)
unnamed: J117.3, U19.5 (D2)
unnamed: J117.4, U19.6 (D3)
unnamed: J118.1, U19.9 (~PE)
unnamed: J118.2, U19.7 (CEP)
unnamed: J118.3, U19.10 (CET)
unnamed: J118.4, U19.2 (CP)
unnamed: J118.5, U19.1 (~MR)
unnamed: J119.1, U18.14 (Q0)
unnamed: J119.2, U18.13 (Q1)
unnamed: J119.3, U18.12 (Q2)
unnamed: J119.4, U18.11 (Q3)
unnamed: J119.5, U18.15 (TC)
unnamed: J120.1, U19.14 (Q0)
unnamed: J120.2, U19.13 (Q1)
unnamed: J120.3, U19.12 (Q2)
unnamed: J120.4, U19.11 (Q3)
unnamed: J120.5, U19.15 (TC)
unnamed: J121.1, U20.2 (Dsr)
unnamed: J121.2, U20.3 (P0)
unnamed: J121.3, U20.4 (P1)
unnamed: J121.4, U20.5 (P2)
unnamed: J121.5, U20.6 (P3)
unnamed: J121.6, U20.7 (Dsl)
unnamed: J122.1, U20.9 (S0)
unnamed: J122.2, U20.10 (S1)
unnamed: J123.1, U20.11 (Cp)
unnamed: J123.2, U20.1 (Mr)
unnamed: J124.1, U21.2 (Dsr)
unnamed: J124.2, U21.3 (P0)
unnamed: J124.3, U21.4 (P1)
unnamed: J124.4, U21.5 (P2)
unnamed: J124.5, U21.6 (P3)
unnamed: J124.6, U21.7 (Dsl)
unnamed: J125.1, U21.9 (S0)
unnamed: J125.2, U21.10 (S1)
unnamed: J126.1, U21.11 (Cp)
unnamed: J126.2, U21.1 (Mr)
unnamed: J127.1, U20.15 (Q0)
unnamed: J127.2, U20.14 (Q1)
unnamed: J127.3, U20.13 (Q2)
unnamed: J127.4, U20.12 (Q3)
unnamed: J128.1, U21.15 (Q0)
unnamed: J128.2, U21.14 (Q1)
unnamed: J128.3, U21.13 (Q2)
unnamed: J128.4, U21.12 (Q3)
unnamed: J129.1, U22.5 (A1)
unnamed: J129.2, U22.3 (A2)
unnamed: J129.3, U22.14 (A3)
unnamed: J129.4, U22.12 (A4)
unnamed: J130.1, U22.6 (B1)
unnamed: J130.2, U22.2 (B2)
unnamed: J130.3, U22.15 (B3)
unnamed: J130.4, U22.11 (B4)
unnamed: J131.1, U23.9 (B0)
unnamed: J131.2, U23.11 (B1)
unnamed: J131.3, U23.14 (B2)
unnamed: J131.4, U23.1 (B3)
unnamed: J132.1, U23.10 (A0)
unnamed: J132.2, U23.12 (A1)
unnamed: J132.3, U23.13 (A2)
unnamed: J132.4, U23.15 (A3)
unnamed: J134.1, U22.4 (S1)
unnamed: J134.2, U22.1 (S2)
unnamed: J134.3, U22.13 (S3)
unnamed: J134.4, U22.10 (S4)
unnamed: J134.5, U22.9 (C4)
unnamed: J135.1, U23.4 (Ia>b)
unnamed: J135.2, U23.2 (Ia<b)
unnamed: J135.3, U23.3 (Ia=b)
unnamed: J136.1, U23.5 (Oa>b)
unnamed: J136.2, U23.7 (Oa<b)
unnamed: J136.3, U23.6 (Oa=b)
unnamed: J138.1, J138.2, U12.6
unnamed: J139.1, SW3.8
unnamed: J139.2, SW3.7
unnamed: J139.3, SW3.6
unnamed: J139.4, SW3.5
unnamed: J140.1, SW4.8
unnamed: J140.2, SW4.7
unnamed: J140.3, SW4.6
unnamed: J140.4, SW4.5
unnamed: J142.1, J142.2, SW6.1
unnamed: J144.1, J144.2, SW8.1
unnamed: J146.1, J146.2, SW10.2 (B)
unnamed: J147.1, J147.2, SW10.5 (B)
unnamed: J148.1, J148.2, SW5.2
unnamed: J149.1, J149.2, SW6.2
unnamed: J150.1, J150.2, SW7.2
unnamed: J151.1, J151.2, SW8.2
unnamed: J154.1, J154.2, SW10.1 (A)
unnamed: J155.1, J155.2, SW10.3 (C)
unnamed: J156.1, J156.2, SW10.4 (A)
unnamed: J157.1, J157.2, SW10.6 (C)
unnamed: DN1.20, J158.1
unnamed: DN1.19, J158.2
unnamed: DN1.18, J158.3
unnamed: DN1.17, J158.4
unnamed: DN1.16, J158.5
unnamed: DN1.15, J158.6
unnamed: DN1.14, J158.7
unnamed: DN1.13, J158.8
unnamed: DN1.12, J158.9
unnamed: DN1.11, J158.10
unnamed: DN2.1, J159.1
unnamed: DN2.2, J159.2
unnamed: DN2.3, J159.3
unnamed: DN2.4, J159.4
unnamed: DN2.5, J159.5
unnamed: DN2.6, J159.6
unnamed: DN2.7, J159.7
unnamed: DN2.8, J159.8
unnamed: DN2.9, J159.9
unnamed: DN2.10, J159.10
unnamed: DN3.20, J160.1
unnamed: DN3.19, J160.2
unnamed: DN3.18, J160.3
unnamed: DN3.17, J160.4
unnamed: DN3.16, J160.5
unnamed: DN3.15, J160.6
unnamed: DN3.14, J160.7
unnamed: DN3.13, J160.8
unnamed: DN3.12, J160.9
unnamed: DN3.11, J160.10
unnamed: J161.1, U25.21 (~RD)
unnamed: J161.2, U25.22 (~WR)
unnamed: J161.3, U25.19 (~MREQ)
unnamed: J161.4, U25.20 (~IORQ)
unnamed: J161.5, U25.27 (~M1)
unnamed: J161.6, U25.28 (~RFSH)
unnamed: J162.1, U25.18 (~HALT)
unnamed: J162.2, U25.24 (~WAIT)
unnamed: J162.3, U25.16 (~INT)
unnamed: J162.4, U25.17 (~NMI)
unnamed: J162.5, U25.26 (~RESET)
unnamed: J162.6, U25.6 (~CLK)
unnamed: J163.1, U25.25 (~BUSRQ)
unnamed: J163.2, U25.23 (~BUSACK)
unnamed: J167.1, U27.20 (~CE)
unnamed: J167.2, U27.22 (~OE)
unnamed: J167.3, U27.27 (~WE)
unnamed: J168.1, U26.20 (~CE)
unnamed: J168.2, U26.22 (~OE)
unnamed: J170.1, SW11.2 (1)
unnamed: J170.2, SW11.3 (2)
unnamed: J170.3, SW11.4
unnamed: J170.4, SW11.5 (8)
unnamed: J171.1, SW12.2 (1)
unnamed: J171.2, SW12.3 (2)
unnamed: J171.3, SW12.4
unnamed: J171.4, SW12.5 (8)
unnamed: R6.2, RV2.2
unnamed: DN1.1, RN3.2 (R1)
unnamed: DN1.2, RN3.3 (R2)
unnamed: DN1.3, RN3.4 (R3)
unnamed: DN1.4, RN3.5 (R4)
unnamed: DN1.5, RN3.6 (R5)
unnamed: DN1.6, RN3.7 (R6)
unnamed: DN1.7, RN3.8 (R7)
unnamed: DN1.8, RN3.9 (R8)
unnamed: DN1.9, RN3.10 (R9)
unnamed: DN1.10, RN3.11 (R10)
unnamed: DN2.20, RN4.2 (R1)
unnamed: DN2.19, RN4.3 (R2)
unnamed: DN2.18, RN4.4 (R3)
unnamed: DN2.17, RN4.5 (R4)
unnamed: DN2.16, RN4.6 (R5)
unnamed: DN2.15, RN4.7 (R6)
unnamed: DN2.14, RN4.8 (R7)
unnamed: DN2.13, RN4.9 (R8)
unnamed: DN2.12, RN4.10 (R9)
unnamed: DN2.11, RN4.11 (R10)
unnamed: DN3.1, RN5.2 (R1)
unnamed: DN3.2, RN5.3 (R2)
unnamed: DN3.3, RN5.4 (R3)
unnamed: DN3.4, RN5.5 (R4)
unnamed: DN3.5, RN5.6 (R5)
unnamed: DN3.6, RN5.7 (R6)
unnamed: DN3.7, RN5.8 (R7)
unnamed: DN3.8, RN5.9 (R8)
unnamed: DN3.9, RN5.10 (R9)
unnamed: DN3.10, RN5.11 (R10)
unnamed: R2.2, SW2.1 (A), U4.1
unnamed: R3.1, SW2.3 (C), U4.5
unnamed: J152.1, J152.2, SW9.1 (A)
unnamed: J145.1, J145.2, SW9.2 (B)
unnamed: J153.1, J153.2, SW9.3 (C)
unnamed: U4.3, U4.4, U12.3
unnamed: U4.2, U4.6, U12.4
unnamed: J137.1, J137.2, U17.12 (C), U24.5 (Q)
unnamed: R7.2, U17.1 (J), U17.4 (K), U17.13 (~R)
unnamed: U12.2, U17.3 (Q)
unnamed: J133.1, J133.2, U22.7 (C0)
unnamed: C22.2, U24.3 (CV)
unnamed: R4.2, R6.1, U24.1 (DIS)
unnamed: C21.2, RV2.3, U24.2 (THR), U24.6 (TR)
unnamed: C23.2, U24.11 (CV)
unnamed: C24.1, R5.2, U24.12 (THR), U24.13 (DIS)
unnamed: U12.5, U24.9 (Q)
unnamed: R1.1, SW1.2, U24.8 (TR)

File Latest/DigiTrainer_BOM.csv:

"Reference","Qty","Value","Footprint","Datasheet"
"C1,C2,C3,C4,C5,C6,C7,C8,C9,C10,C11,C12,C13,C14,C15,C16,C17,C18,C19,C20,C25,C26,C27,C28,C29,C30","26","0.1uF","Capacitor_SMD:C_0805_2012Metric_Pad1.18x1.45mm_HandSolder","~"
"C21,C24","2","1uF","Capacitor_SMD:C_0805_2012Metric_Pad1.18x1.45mm_HandSolder","~"
"C22,C23","2","0.01uF","Capacitor_SMD:C_0805_2012Metric_Pad1.18x1.45mm_HandSolder","~"
"D1,D2","2","D_Schottky","Diode_THT:D_DO-41_SOD81_P7.62mm_Horizontal","~"
"DN1,DN2,DN3","3","LED Array","Package_DIP:DIP-20_W7.62mm_Socket","~"
"J1,J2,J86,J158,J159,J160","6","Conn_01x10","Connector_PinSocket_2.54mm:PinSocket_1x10_P2.54mm_Vertical","~"
"J3,J16,J17,J18,J19,J20,J21,J22,J23,J24,J25,J26,J27,J28,J29,J30,J31,J54,J55,J56,J57,J58,J59,J60,J61,J62,J63,J64,J65,J66,J67,J68,J69,J89,J99,J100,J102,J109,J110,J111,J112,J113,J114,J122,J123,J125,J126,J133,J137,J138,J142,J144,J145,J146,J147,J148,J149,J150,J151,J152,J153,J154,J155,J156,J157,J163,J168","67","Conn_01x02","Connector_PinSocket_2.54mm:PinSocket_1x02_P2.54mm_Vertical","~"
"J4,J5,J6,J7,J8,J9,J10,J11,J12,J13,J14,J15,J32,J33,J34,J35,J36,J37,J38,J39,J40,J41,J42,J43,J44,J45,J46,J47,J48,J49,J50,J51,J52,J53,J70,J71,J72,J73,J74,J75,J76,J77,J78,J79,J80,J81,J87,J106,J107,J108,J135,J136,J141,J143,J167,J169","56","Conn_01x03","Connector_PinSocket_2.54mm:PinSocket_1x03_P2.54mm_Vertical","~"
"J82,J83,J84,J85,J98,J103,J121,J124,J161,J162","10","Conn_01x06","Connector_PinSocket_2.54mm:PinSocket_1x06_P2.54mm_Vertical","~"
"J88,J90,J91,J101,J104,J105,J164,J165,J166,J173,J174","11","Conn_01x08","Connector_PinSocket_2.54mm:PinSocket_1x08_P2.54mm_Vertical","~"
"J92,J93,J94,J172","4","Conn_02x02_Odd_Even","Connector_PinHeader_2.54mm:PinHeader_2x02_P2.54mm_Vertical","~"
"J95","1","Barrel_Jack_Switch","Connector_BarrelJack:BarrelJack_Horizontal","~"
"J96","1","USB_B_Mini","Connector_USB:USB_Mini-B_Tensility_54-00023_Vertical","~"
"J97,J115,J117,J127,J128,J129,J130,J131,J132,J139,J140,J170,J171","13","Conn_01x04","Connector_PinSocket_2.54mm:PinSocket_1x04_P2.54mm_Vertical","~"
"J116,J118,J119,J120,J134","5","Conn_01x05","Connector_PinSocket_2.54mm:PinSocket_1x05_P2.54mm_Vertical","~"
"R1,R2,R3","3","10k","Resistor_SMD:R_0805_2012Metric_Pad1.20x1.40mm_HandSolder","~"
"R4,R5,R6,R7","4","1k","Resistor_SMD:R_0805_2012Metric_Pad1.20x1.40mm_HandSolder","~"
"RN1,RN2,RN3,RN4,RN5","5","R_Network10","Resistor_THT:R_Array_SIP11","http://www.vishay.com/docs/31509/csc.pdf"
"RV1","1","R_Potentiometer","Potentiometer_THT:Potentiometer_Bourns_3386P_Vertical","~"
"RV2","1","1M","Potentiometer_THT:Potentiometer_Bourns_3386P_Vertical","~"
"SW1,SW5,SW6,SW7,SW8","5","SW_Push","RetroStackLibrary:SW_SPST_Push","~"
"SW2","1","SW_DPDT_x2","RetroStackLibrary:SW_DPDT_Push","~"
"SW3,SW4","2","SW_DIP_x04","Package_DIP:DIP-8_W7.62mm","~"
"SW9","1","SW_SPDT","RetroStackLibrary:SW_SPDT_Toggle","~"
"SW10","1","SW_Push_DPDT","RetroStackLibrary:SW_DPDT_Slide_RightAngle","~"
"SW11,SW12","2","Hex Switch","RetroStackLibrary:SW_Hexadecimal_Horizontal","https://www.ckswitches.com/media/1333/cd.pdf"
"U1","1","74LS07","Package_SO:SOIC-14_3.9x8.7mm_P1.27mm","www.ti.com/lit/ds/symlink/sn74ls07.pdf"
"U2","1","74LS04","Package_SO:SOIC-14_3.9x8.7mm_P1.27mm","http://www.ti.com/lit/gpn/sn74LS04"
"U3","1","74LS266","Package_SO:SOIC-14_3.9x8.7mm_P1.27mm",""
"U4,U5","2","74LS00","Package_SO:SOIC-14_3.9x8.7mm_P1.27mm","http://www.ti.com/lit/gpn/sn74ls00"
"U6","1","74LS08","Package_SO:SOIC-14_3.9x8.7mm_P1.27mm","http://www.ti.com/lit/gpn/sn74LS08"
"U7","1","74LS86","Package_SO:SOIC-14_3.9x8.7mm_P1.27mm","74xx/74ls86.pdf"
"U8","1","74LS32","Package_SO:SOIC-14_3.9x8.7mm_P1.27mm","http://www.ti.com/lit/gpn/sn74LS32"
"U9","1","74LS02","Package_SO:SOIC-14_3.9x8.7mm_P1.27mm","http://www.ti.com/lit/gpn/sn74ls02"
"U10","1","74LS244","Package_SO:SOIC-20W_7.5x12.8mm_P1.27mm","http://www.ti.com/lit/ds/symlink/sn74ls244.pdf"
"U11","1","74LS245","Package_SO:SO-20_5.3x12.6mm_P1.27mm","http://www.ti.com/lit/gpn/sn74LS245"
"U12","1","74LS51","Package_SO:SOIC-14_3.9x8.7mm_P1.27mm","http://www.ti.com/lit/ds/symlink/sn74ls51.pdf"
"U13","1","74LS174","Package_SO:SOIC-16_3.9x9.9mm_P1.27mm","http://www.ti.com/lit/gpn/sn74LS174"
"U14","1","74LS175","Package_SO:SOIC-16_3.9x9.9mm_P1.27mm","http://www.ti.com/lit/gpn/sn74LS175"
"U15","1","74LS373","Package_SO:SO-20_5.3x12.6mm_P1.27mm","http://www.ti.com/lit/gpn/sn74LS373"
"U16","1","74LS112","Package_SO:SOIC-16_3.9x9.9mm_P1.27mm","http://www.ti.com/lit/gpn/sn74LS112"
"U17","1","74LS107","Package_SO:SOIC-14_3.9x8.7mm_P1.27mm","http://www.ti.com/lit/gpn/sn74LS107"
"U18","1","74LS161","Package_SO:SOIC-16_3.9x9.9mm_P1.27mm","http://www.ti.com/lit/gpn/sn74LS161"
"U19","1","74LS163","Package_SO:SOIC-16_3.9x9.9mm_P1.27mm","http://www.ti.com/lit/gpn/sn74LS163"
"U20,U21","2","74LS194","Package_SO:SOIC-16_3.9x9.9mm_P1.27mm","http://www.ti.com/lit/gpn/sn74LS194"
"U22","1","74LS283","Package_SO:SOIC-16_3.9x9.9mm_P1.27mm","http://www.ti.com/lit/gpn/sn74LS283"
"U23","1","74LS85","Package_SO:SOIC-16_3.9x9.9mm_P1.27mm","http://www.ti.com/lit/gpn/sn74LS85"
"U24","1","NE556","Package_SO:SOIC-14_3.9x8.7mm_P1.27mm","http://www.ti.com/lit/ds/symlink/ne556.pdf"
"U25","1","Z80CPU","Package_DIP:DIP-40_W15.24mm_Socket","www.zilog.com/manage_directlink.php?filepath=docs/z80/um0080"
"U26","1","ROM_27256","Package_DIP:DIP-28_W15.24mm",""
"U27","1","CY7C199","Package_DIP:DIP-28_W7.62mm",""

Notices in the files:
README.md:
License:
This project is licensed under the MIT License - see the [LICENSE](LICENSE) file for details.
